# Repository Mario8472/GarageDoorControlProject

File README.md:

# GarageDoorControlProject
Hardware and Software for Garage door control (retrofit) 

   Project:    Garage Door Control Unit
   MCU:        PIC18F45K22
   Hardware:   Garage Door Control PCB Card
   Software:   mikroC PRO for PIC18
   Author:     Mario Oletić
   
   Project description:
   -----------------------------------------------------------------------------
   This project is developed (both hardware and software) for replacing/retrofit
   the old garage door PCB. PCB has six input signals (24VDC level). Two of 
   them are used for starting the door movements (opening or closing). Doors can
   be started with radio switch (Input1) with 24VDC signal output or some other 
   common switch (Input2). Other four inputs are used for external capacitive or
   inductive sensors to determine door position - two for UP and DOWN positions 
   and two to determine a position of doors while approaching CLOSE or OPEN 
   positions. The last two positions are used for slowing the doors down. 
   Signals on INPUT1 and INPUT2 are switching between four working modes. MODE 0 
   and MODE2 are for stoping, MODE1 for opening and MODE3 for closing the doors.
   Outputs are used for controlling the 24V DC motor with PWM signals. Depending 
   on the door position, the motor can rotate with two different speeds (speed 
   depends on the PWM duty cycle) - one is for normal door speed and the other 
   (slower) is for approaching final positions. Also, when activating the door, 
   lights turn on. There are two outputs for 24V DC LED lights and one output 
   for 230V AC light bulb which is controlled via Triac. Triac is triggered with 
   OptoTriac IC with zero-cross detection circuit. Also, OptoTriac isolates 230V 
   AC system from the rest of the PCB low voltage systems. Lights will be turned 
   off after doors are stoped, no matter in what position, after a fixed period 
   of time passes. When doors are not moving, MCU goes into sleep mode with much 
   lower current consumption. When a new signal for activating the doors appears, 
   MCU wakes up.

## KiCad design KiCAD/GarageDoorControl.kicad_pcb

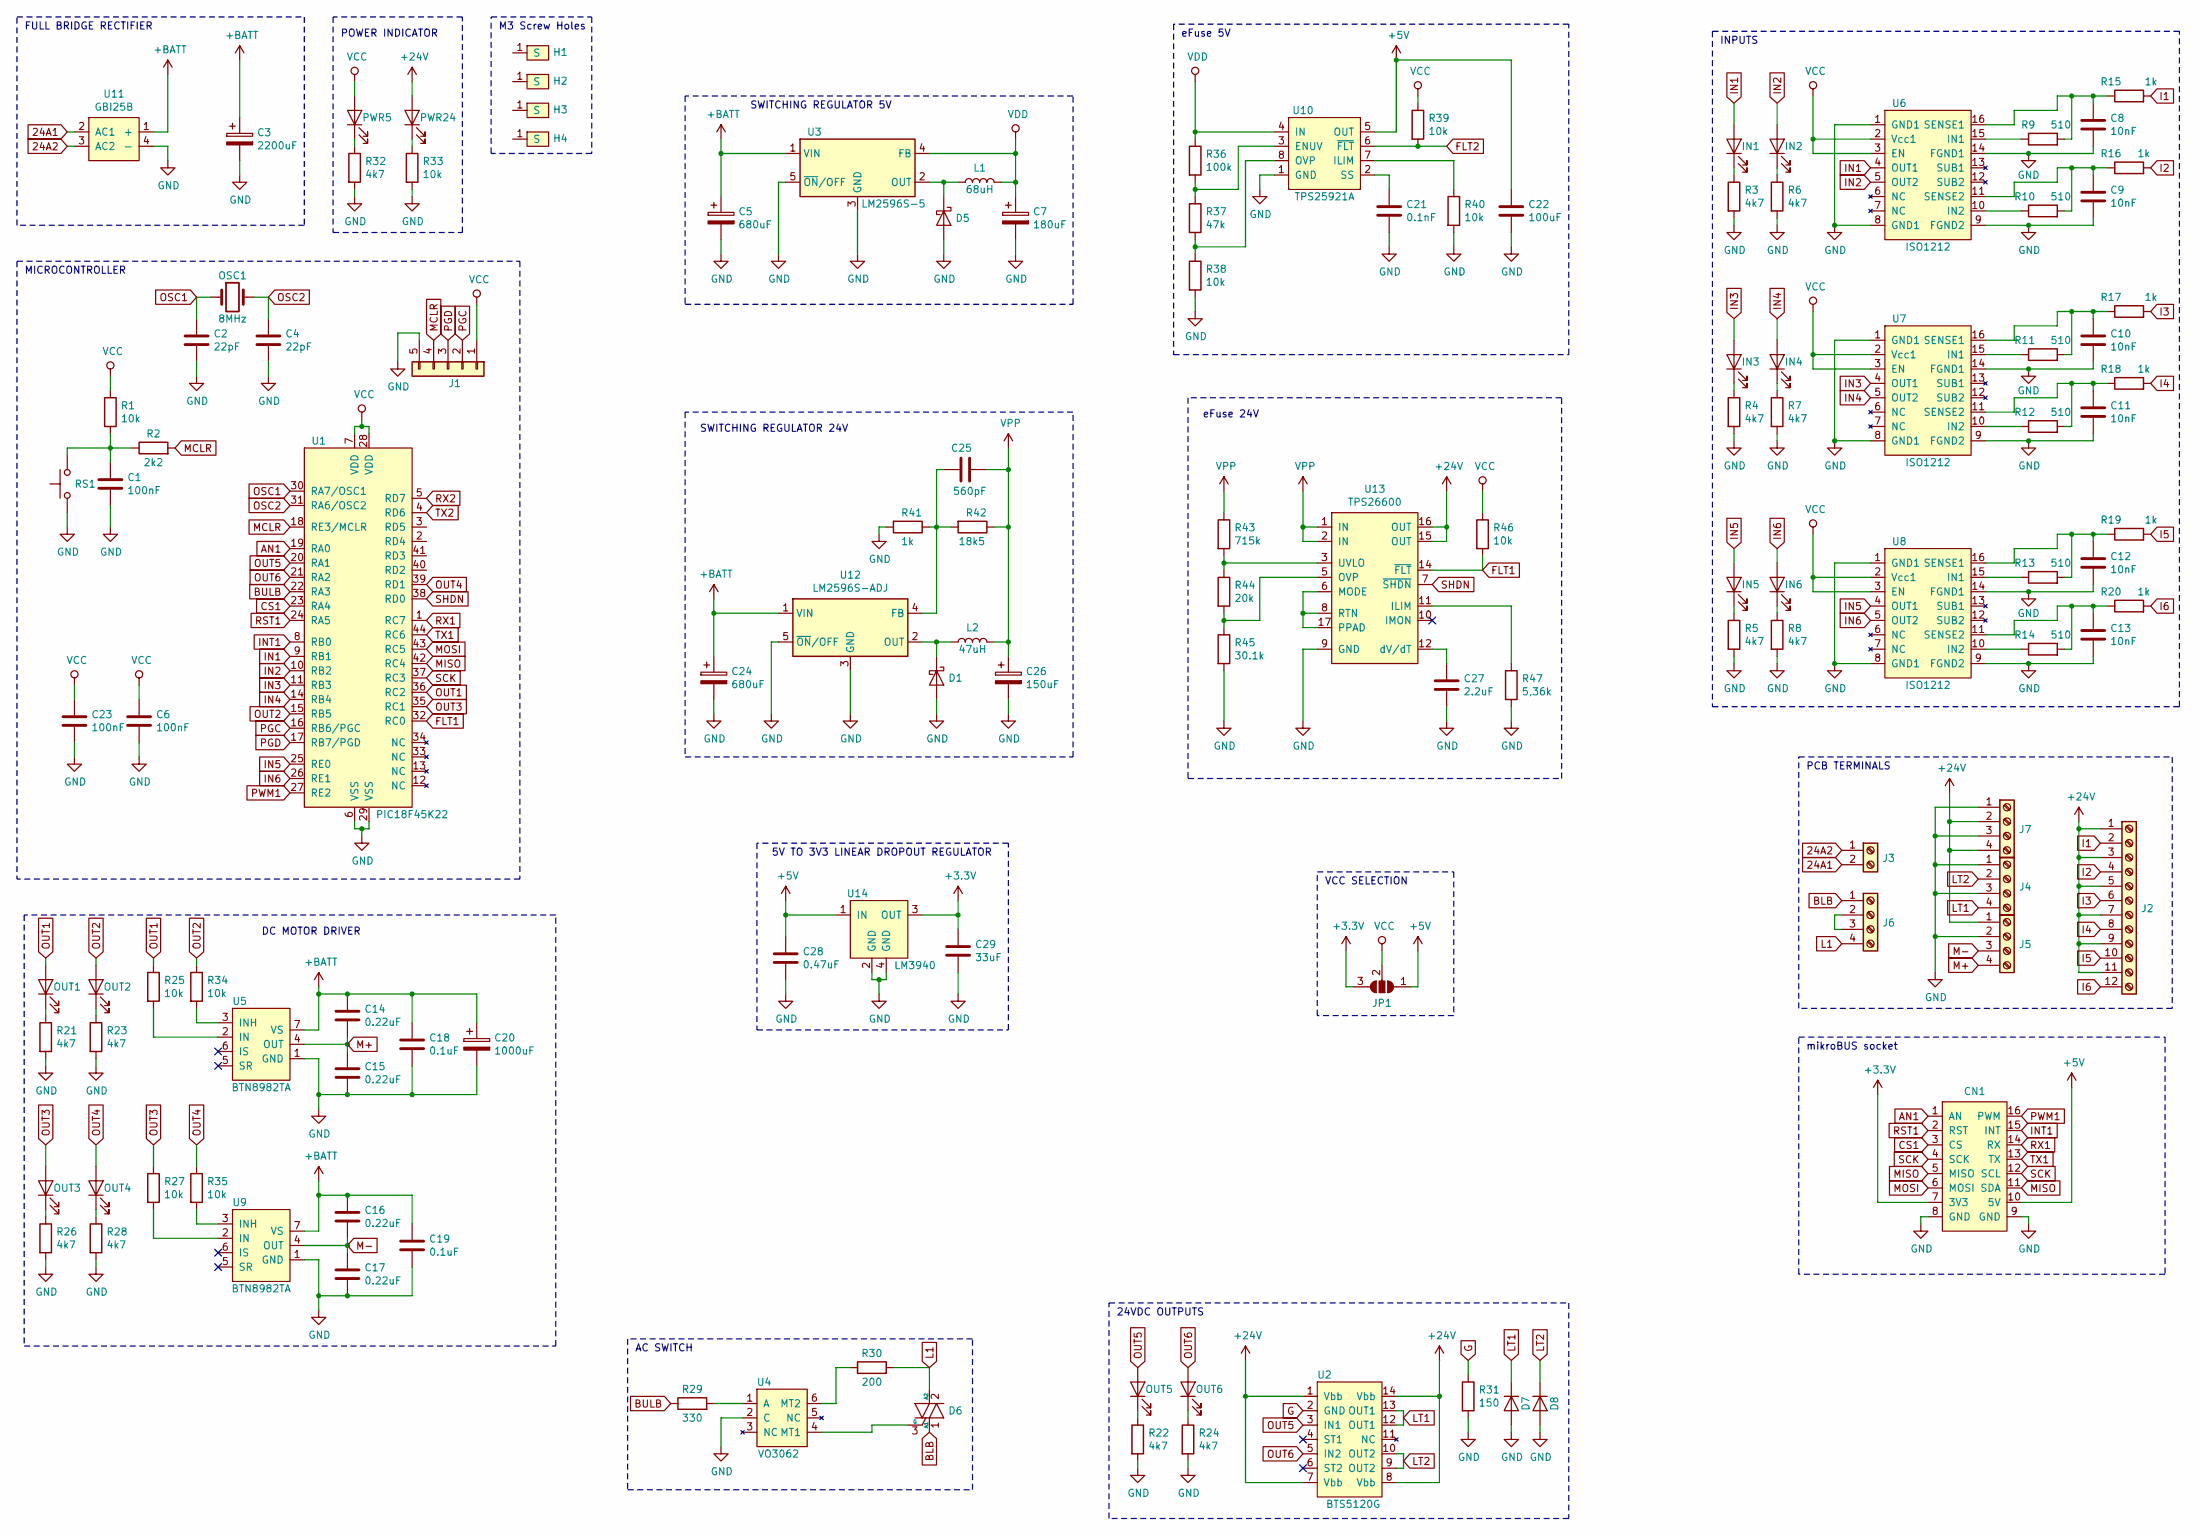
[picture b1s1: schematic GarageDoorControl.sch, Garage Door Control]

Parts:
C1, C6, C23: 100nF; C_0805_2012Metric
C2, C4: 22pF; C_0805_2012Metric
C3: 2200uF; CP_Radial_D16.0mm_P7.50mm
C5, C24: 680uF; CP_Radial_D12.5mm_P5.00mm
C7: 180uF; CP_Radial_D8.0mm_P3.50mm
C8, C9, C10, C11, C12, C13: 10nF; C_0805_2012Metric
C14, C15, C16, C17: 0.22uF; C_0805_2012Metric
C18, C19: 0.1uF; C_0805_2012Metric
C20: 1000uF; CP_Radial_D16.0mm_P7.50mm
C21: 0.1nF; C_0805_2012Metric
C22: 100uF; C_0805_2012Metric
C25: 560pF; C_0805_2012Metric
C26: 150uF; CP_Radial_D10.0mm_P5.00mm
C27: 2.2uF; C_0805_2012Metric
C28: 0.47uF; C_0805_2012Metric
C29: 33uF; C_0805_2012Metric
CN1: mikroBUS_socket
D1, D5: D_Schottky; D_DO-201AD_P12.70mm_Horizontal
D6: Q_TRIAC_A1A2G; TO-252-2
D7, D8: D; D_SOD-323
H1, H2, H3, H4: ScrewHoleM3
IN1, IN2, IN3, IN4, IN5, IN6: LED; LED_0805_2012Metric
J1: Conn_01x05; PinHeader_1x05_P2.54mm_Vertical
J2: Screw_Terminal_01x12; PCB_Screw_Terminal_5.08_12ways
J3: Screw_Terminal_01x02; PCB_Screw_Terminal_5.08_2ways
J4, J5, J6, J7: Screw_Terminal_01x04; PCB_Screw_Terminal_5.08_4ways
JP1: SolderJumper_3_Open; Jumper_0805
L1: 68uH; HPI1206
L2: 47uH; HPI1206
OSC1: 8MHz; Crystal_SMD_HC49-SD
OUT1, OUT2, OUT3, OUT4, OUT5, OUT6: LED; LED_0805_2012Metric
PWR5, PWR24: LED; LED_0805_2012Metric
R1, R25, R27, R34, R35, R38, R39, R40, R46: 10k; R_0805_2012Metric
R2: 2k2; R_0805_2012Metric
R3, R4, R5, R6, R7, R8, R21, R22, R23, R24, R26, R28, R32: 4k7; R_0805_2012Metric
R9, R10, R11, R12, R13, R14: 510; R_1206_3216Metric
R15, R16, R17, R18, R19, R20: 1k; R_1206_3216Metric
R29: 330; R_0805_2012Metric
R30: 200; R_2512_6332Metric
R31: 150; R_0805_2012Metric
R33: 10k; R_1206_3216Metric
R36: 100k; R_0805_2012Metric
R37: 47k; R_0805_2012Metric
R41: 1k; R_0805_2012Metric
R42: 18k5; R_0805_2012Metric
R43: 715k; R_0805_2012Metric
R44: 20k; R_0805_2012Metric
R45: 30.1k; R_0805_2012Metric
R47: 5,36k; R_0805_2012Metric
RS1: SW_Push; TACTSWITCH6x6
U1: PIC18F45K22; TQFP-44_10x10mm_P0.8mm
U2: BTS5120G; SOIC-14_3.9x8.7mm_P1.27mm
U3: LM2596S-5; TO-263-5_TabPin3
U4: VO3062; SMDIP-6_W9.53mm
U5, U9: BTN8982TA; TO-263-7_TabPin4
U6, U7, U8: ISO1212
U10: TPS25921A; SOIC-8_3.9x4.9mm_P1.27mm
U11: GBI25B; DiodeBridge_GBI
U12: LM2596S-ADJ; TO-263-5_TabPin3
U13: TPS26600; HTSSOP-16-1EP_4.4x5mm_P0.65mm_EP3x3mm
U14: LM3940; SOT-223

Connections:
24A1: J3.2, U11.2 (AC1)
24A2: J3.1, U11.3 (AC2)
+3V3: C29.1, CN1.7 (3V3), JP1.3 (B), U14.3 (OUT)
+5V: C22.1, C28.1, CN1.10 (5V), JP1.1 (A), U10.5 (OUT), U14.1 (IN)
+24V: J2.1, J2.3, J2.5, J2.7, J2.9, J2.11, J5.1, J7.2, J7.4, PWR24.2 (A), U2.1 (Vbb), U2.7 (Vbb), U2.8 (Vbb), U2.14 (Vbb), U13.15 (OUT), U13.16 (OUT)
+BATT: C3.1, C5.1, C14.1, C16.1, C18.1, C19.1, C20.1, C24.1, U3.1 (VIN), U5.7 (VS), U9.7 (VS), U11.1 (+), U12.1 (VIN)
AN1: CN1.1 (AN), U1.19 (RA0)
BLB: D6.1 (A1), J6.1
BULB: R29.1, U1.22 (RA3)
CS1: CN1.3 (CS), U1.23 (RA4)
FLT1: R46.2, U1.32 (RC0), U13.14 (~FLT)
FLT2: R39.2, U10.6 (~FLT)
G: R31.1, U2.2 (GND)
GND: C1.2, C2.2, C3.2, C4.2, C5.2, C6.2, C7.2, C8.2, C9.2, C10.2, C11.2, C12.2, C13.2, C15.2, C17.2, C18.2, C19.2, C20.2, C21.2, C22.2, C23.2, C24.2, C26.2, C27.2, C28.2, C29.2, CN1.8 (GND), CN1.9 (GND), D1.2 (A), D5.2 (A), D7.2 (A), D8.2 (A), J1.5, J4.1, J4.3, J5.2, J7.1, J7.3, R3.2, R4.2, R5.2, R6.2, R7.2, R8.2, R21.2, R22.2, R23.2, R24.2, R26.2, R28.2, R31.2, R32.2, R33.2, R38.2, R40.2, R41.2, R45.2, R47.2, RS1.1, U1.6 (VSS), U1.29 (VSS), U3.3 (GND), U3.5 (~ON~/OFF), U4.2 (C), U5.1 (GND), U6.1 (GND1), U6.8 (GND1), U6.9 (FGND2), U6.14 (FGND1), U7.1 (GND1), U7.8 (GND1), U7.9 (FGND2), U7.14 (FGND1), U8.1 (GND1), U8.8 (GND1), U8.9 (FGND2), U8.14 (FGND1), U9.1 (GND), U10.1 (GND), U11.4 (-), U12.3 (GND), U12.5 (~ON~/OFF), U13.9 (GND), U14.2 (GND), U14.4 (GND)
I1: J2.2, R15.2
I2: J2.4, R16.2
I3: J2.6, R17.2
I4: J2.8, R18.2
I5: J2.10, R19.2
I6: J2.12, R20.2
IN1: IN1.2 (A), U1.9 (RB1), U6.4 (OUT1)
IN2: IN2.2 (A), U1.10 (RB2), U6.5 (OUT2)
IN3: IN3.2 (A), U1.11 (RB3), U7.4 (OUT1)
IN4: IN4.2 (A), U1.14 (RB4), U7.5 (OUT2)
IN5: IN5.2 (A), U1.25 (RE0), U8.4 (OUT1)
IN6: IN6.2 (A), U1.26 (RE1), U8.5 (OUT2)
INT1: CN1.15 (INT), U1.8 (RB0)
L1: D6.2 (A2), J6.4, R30.2
LT1: D7.1 (K), J4.4, U2.12 (OUT1), U2.13 (OUT1)
LT2: D8.1 (K), J4.2, U2.9 (OUT2), U2.10 (OUT2)
M+: C14.2, C15.1, J5.4, U5.4 (OUT)
M-: C16.2, C17.1, J5.3, U9.4 (OUT)
MCLR: J1.4, R2.2, U1.18 (RE3/MCLR)
MISO: CN1.5 (MISO), CN1.11 (SDA), U1.42 (RC4)
MOSI: CN1.6 (MOSI), U1.43 (RC5)
unnamed: C1.1, R1.2, R2.1, RS1.2
unnamed: C8.1, R9.2, R15.1, U6.16 (SENSE1)
unnamed: C9.1, R10.2, R16.1, U6.11 (SENSE2)
unnamed: C10.1, R11.2, R17.1, U7.16 (SENSE1)
unnamed: C11.1, R12.2, R18.1, U7.11 (SENSE2)
unnamed: C12.1, R13.2, R19.1, U8.16 (SENSE1)
unnamed: C13.1, R14.2, R20.1, U8.11 (SENSE2)
unnamed: C21.1, U10.2 (SS)
unnamed: C25.1, R41.1, R42.2, U12.4 (FB)
unnamed: C27.1, U13.12 (dV/dT)
unnamed: D1.1 (K), L2.1, U12.2 (OUT)
unnamed: D5.1 (K), L1.1, U3.2 (OUT)
unnamed: D6.3 (G), U4.4 (MT1)
unnamed: IN1.1 (K), R3.1
unnamed: IN2.1 (K), R6.1
unnamed: IN3.1 (K), R4.1
unnamed: IN4.1 (K), R7.1
unnamed: IN5.1 (K), R5.1
unnamed: IN6.1 (K), R8.1
unnamed: J6.2, J6.3
unnamed: OUT1.1 (K), R21.1
unnamed: OUT2.1 (K), R23.1
unnamed: OUT3.1 (K), R26.1
unnamed: OUT4.1 (K), R28.1
unnamed: OUT5.1 (K), R22.1
unnamed: OUT6.1 (K), R24.1
unnamed: PWR5.1 (K), R32.1
unnamed: PWR24.1 (K), R33.1
unnamed: R9.1, U6.15 (IN1)
unnamed: R10.1, U6.10 (IN2)
unnamed: R11.1, U7.15 (IN1)
unnamed: R12.1, U7.10 (IN2)
unnamed: R13.1, U8.15 (IN1)
unnamed: R14.1, U8.10 (IN2)
unnamed: R25.2, U5.2 (IN)
unnamed: R27.2, U9.2 (IN)
unnamed: R29.2, U4.1 (A)
unnamed: R30.1, U4.6 (MT2)
unnamed: R34.2, U5.3 (INH)
unnamed: R35.2, U9.3 (INH)
unnamed: R36.2, R37.1, U10.3 (ENUV)
unnamed: R37.2, R38.1, U10.8 (OVP)
unnamed: R40.1, U10.7 (ILIM)
unnamed: R43.2, R44.1, U13.3 (UVLO)
unnamed: R44.2, R45.1, U13.5 (OVP)
unnamed: R47.1, U13.11 (ILIM)
unnamed: U13.6 (MODE), U13.8 (RTN), U13.17 (PPAD)
OSC1: C2.1, OSC1.1, U1.30 (RA7/OSC1)
OSC2: C4.1, OSC1.2, U1.31 (RA6/OSC2)
OUT1: OUT1.2 (A), R25.1, U1.36 (RC2)
OUT2: OUT2.2 (A), R34.1, U1.15 (RB5)
OUT3: OUT3.2 (A), R27.1, U1.35 (RC1)
OUT4: OUT4.2 (A), R35.1, U1.39 (RD1)
OUT5: OUT5.2 (A), U1.20 (RA1), U2.3 (IN1)
OUT6: OUT6.2 (A), U1.21 (RA2), U2.5 (IN2)
PGC: J1.2, U1.16 (RB6/PGC)
PGD: J1.3, U1.17 (RB7/PGD)
PWM1: CN1.16 (PWM), U1.27 (RE2)
RST1: CN1.2 (RST), U1.24 (RA5)
RX1: CN1.14 (RX), U1.1 (RC7)
RX2: U1.5 (RD7)
SCK: CN1.4 (SCK), CN1.12 (SCL), U1.37 (RC3)
SHDN: U1.38 (RD0), U13.7 (~SHDN)
TX1: CN1.13 (TX), U1.44 (RC6)
TX2: U1.4 (RD6)
VCC: C6.1, C23.1, J1.1, JP1.2 (C), PWR5.2 (A), R1.1, R39.1, R46.1, U1.7 (VDD), U1.28 (VDD), U6.2 (Vcc1), U6.3 (EN), U7.2 (Vcc1), U7.3 (EN), U8.2 (Vcc1), U8.3 (EN)
VDD: C7.1, L1.2, R36.1, U3.4 (FB), U10.4 (IN)
VPP: C25.2, C26.1, L2.2, R42.1, R43.1, U13.1 (IN), U13.2 (IN)

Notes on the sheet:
FULL BRIDGE RECTIFIER
SWITCHING REGULATOR 5V
MICROCONTROLLER
INPUTS
DC MOTOR DRIVER
24VDC OUTPUTS
AC SWITCH
PCB TERMINALS
mikroBUS socket
POWER INDICATOR
eFuse 5V
M3 Screw Holes
SWITCHING REGULATOR 24V
eFuse 24V
5V TO 3V3 LINEAR DROPOUT REGULATOR
VCC SELECTION

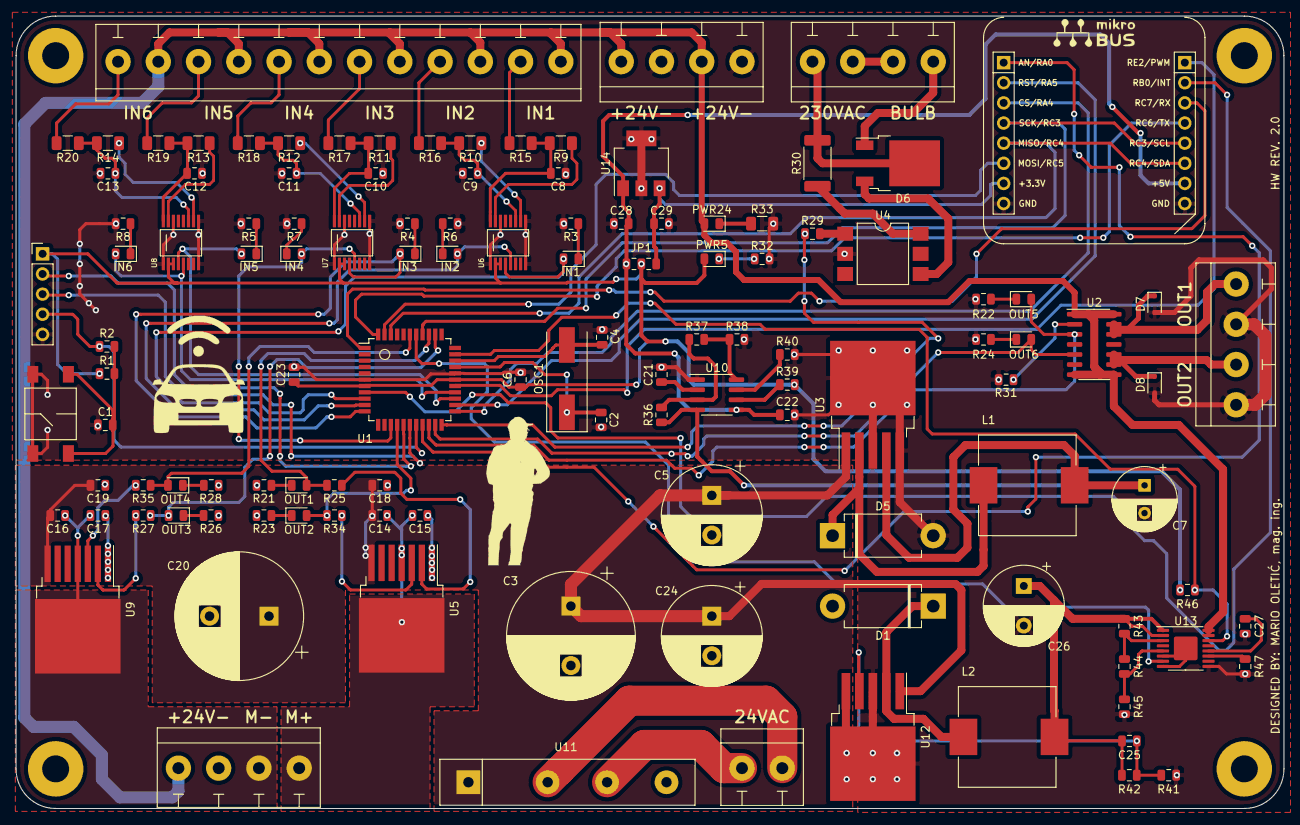
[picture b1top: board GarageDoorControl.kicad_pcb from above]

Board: 2 copper layers, 160.0 x 100.0 mm, 126 parts (0 on the bottom side), 101 nets.

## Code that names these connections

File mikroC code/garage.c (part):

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       T0CON.TMR0ON = 0;
       
       // Turn off the lights
       BULB = 0;
       LED_LIGHT1 = 0;
       LED_LIGHT2 = 0;
       
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// Turn on the lights
void Lights_On()
{
   BULB = 1;
   LED_LIGHT1 = 1;
   LED_LIGHT2 = 1;
   
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     /************************************************************
                       Flags setting
     *************************************************************/
     // Signal for opening/closing appears - IN1 (RB1 pin)
     if (Button(&PORTB, 1, 1, 1))
     {
        start_state = 1;
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        start_state = 0;
     }
     
     // Signal for opening/closing appears - IN2 (RB2 pin)
     if (Button(&PORTB, 2, 1, 1))
     {
        start_state2 = 1;
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        start_state2 = 0;
     }
     
     // Signal for door_closed - IN4 (RB4 pin)
     if(Button(&PORTB, 4, 1, 1))
     {
        door_down = 1;
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     {
        door_down = 0;
     }
     // Signal for door_up - IN3 (RB3 pin)
     if(Button(&PORTB, 3, 1, 1))
     {
        door_up = 1;
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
